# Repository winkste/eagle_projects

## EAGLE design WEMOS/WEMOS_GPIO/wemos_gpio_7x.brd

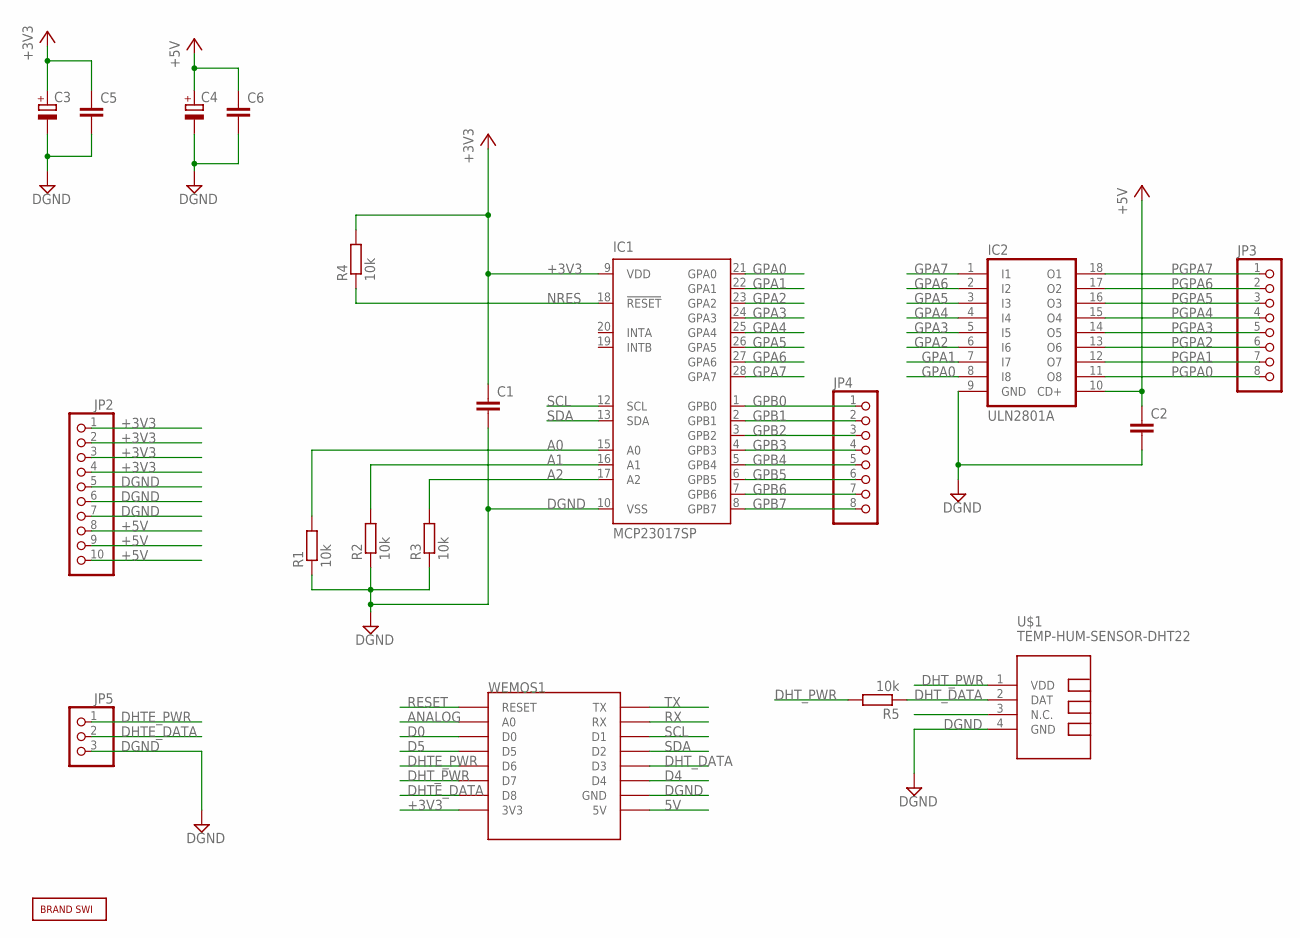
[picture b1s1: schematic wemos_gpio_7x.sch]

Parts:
C1, C2, C5, C6: C-EUC1210; C1210
C3, C4: CPOL-EUTT5D7; TT5D7
IC1: MCP23017SP; DIL28-3
IC2: ULN2801A; DIL18
JP2: PINHD-1X10; 1X10
JP3, JP4: PINHD-1X8; 1X08
JP5: PINHD-1X3; 1X03
R1, R2, R3, R4, R5: 10k; M1206
U$1: TEMP-HUM-SENSOR-DHT22
U$2: BRAND_SWI5X7; BRAND_SWI_5X7
WEMOS1: WEMOS-D1-MINI

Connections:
5V: WEMOS1.5V
+3V3: C1.1, C3.+, C5.1, IC1.9 (VDD), JP2.1, JP2.2, JP2.3, JP2.4, R4.2, WEMOS1.3V3
+5V: C2.1, C4.+, C6.1, IC2.10 (CD+), JP2.8, JP2.9, JP2.10
A0: IC1.15 (A0), R1.2
A1: IC1.16 (A1), R2.2
A2: IC1.17 (A2), R3.2
ANALOG: WEMOS1.A0
D0: WEMOS1.D0
D4: WEMOS1.D4
D5: WEMOS1.D5
DGND: C1.2, C2.2, C3.-, C4.-, C5.2, C6.2, IC1.10 (VSS), IC2.9 (GND), JP2.5, JP2.6, JP2.7, JP5.3, R1.1, R2.1, R3.1, U$1.4 (GND), WEMOS1.GND
DHTE_DATA: JP5.2, WEMOS1.D8
DHTE_PWR: JP5.1, WEMOS1.D6
DHT_DATA: R5.1, U$1.2 (DAT), WEMOS1.D3
DHT_PWR: R5.2, U$1.1 (VDD), WEMOS1.D7
GPA0: IC1.21 (GPA0), IC2.8 (I8)
GPA1: IC1.22 (GPA1), IC2.7 (I7)
GPA2: IC1.23 (GPA2), IC2.6 (I6)
GPA3: IC1.24 (GPA3), IC2.5 (I5)
GPA4: IC1.25 (GPA4), IC2.4 (I4)
GPA5: IC1.26 (GPA5), IC2.3 (I3)
GPA6: IC1.27 (GPA6), IC2.2 (I2)
GPA7: IC1.28 (GPA7), IC2.1 (I1)
GPB0: IC1.1 (GPB0), JP4.1
GPB1: IC1.2 (GPB1), JP4.2
GPB2: IC1.3 (GPB2), JP4.3
GPB3: IC1.4 (GPB3), JP4.4
GPB4: IC1.5 (GPB4), JP4.5
GPB5: IC1.6 (GPB5), JP4.6
GPB6: IC1.7 (GPB6), JP4.7
GPB7: IC1.8 (GPB7), JP4.8
NRES: IC1.18 (!RESET), R4.1
PGPA0: IC2.11 (O8), JP3.8
PGPA1: IC2.12 (O7), JP3.7
PGPA2: IC2.13 (O6), JP3.6
PGPA3: IC2.14 (O5), JP3.5
PGPA4: IC2.15 (O4), JP3.4
PGPA5: IC2.16 (O3), JP3.3
PGPA6: IC2.17 (O2), JP3.2
PGPA7: IC2.18 (O1), JP3.1
RESET: WEMOS1.RESET
RX: WEMOS1.RX
SCL: IC1.12 (SCL), WEMOS1.D1
SDA: IC1.13 (SDA), WEMOS1.D2

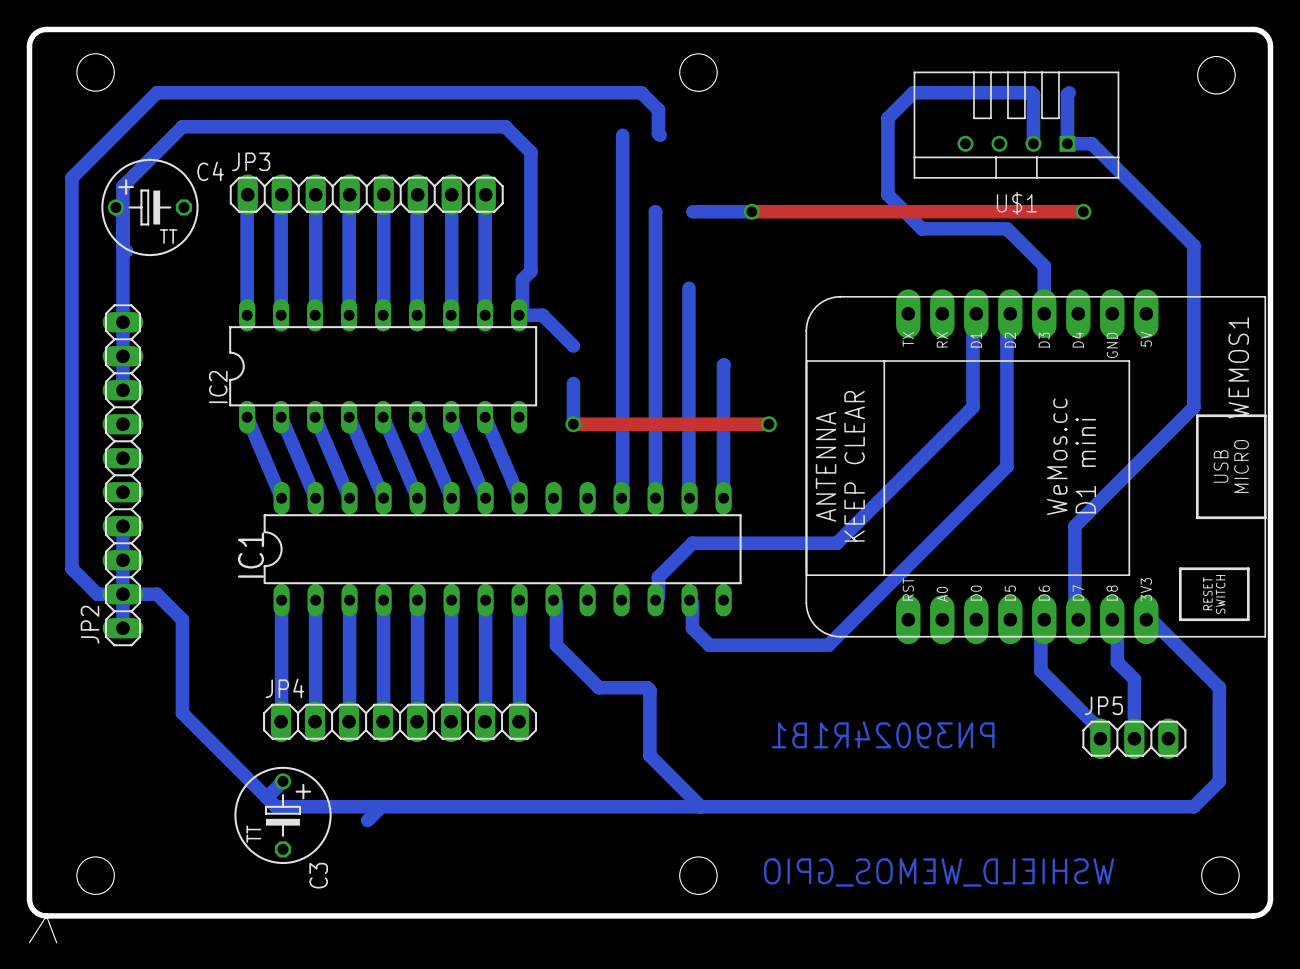
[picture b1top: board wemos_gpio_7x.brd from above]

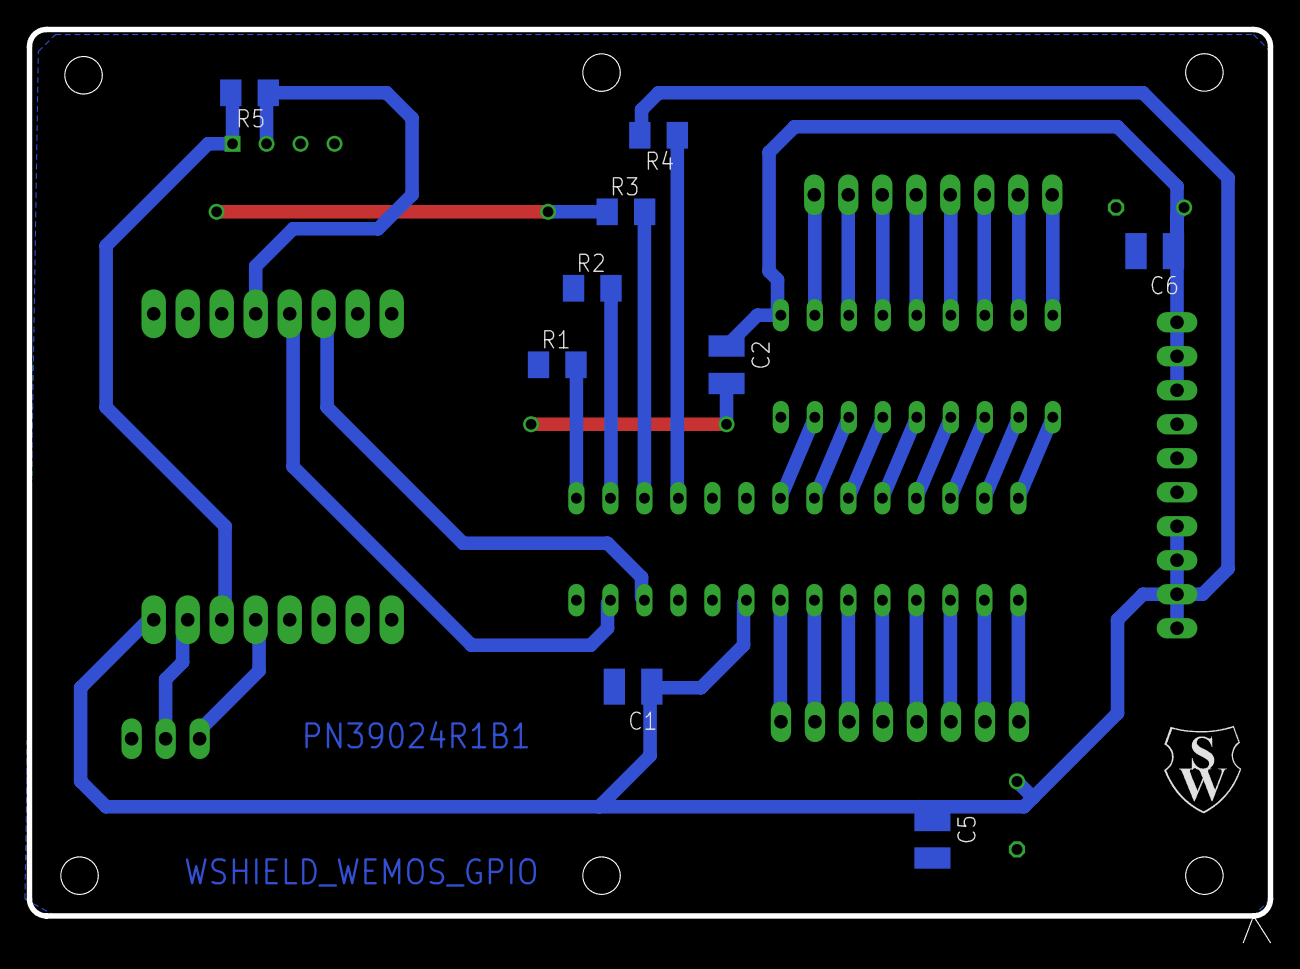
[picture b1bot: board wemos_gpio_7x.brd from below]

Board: 2 copper layers, 92.7 x 68.2 mm, 20 parts (10 on the bottom side), 37 nets.

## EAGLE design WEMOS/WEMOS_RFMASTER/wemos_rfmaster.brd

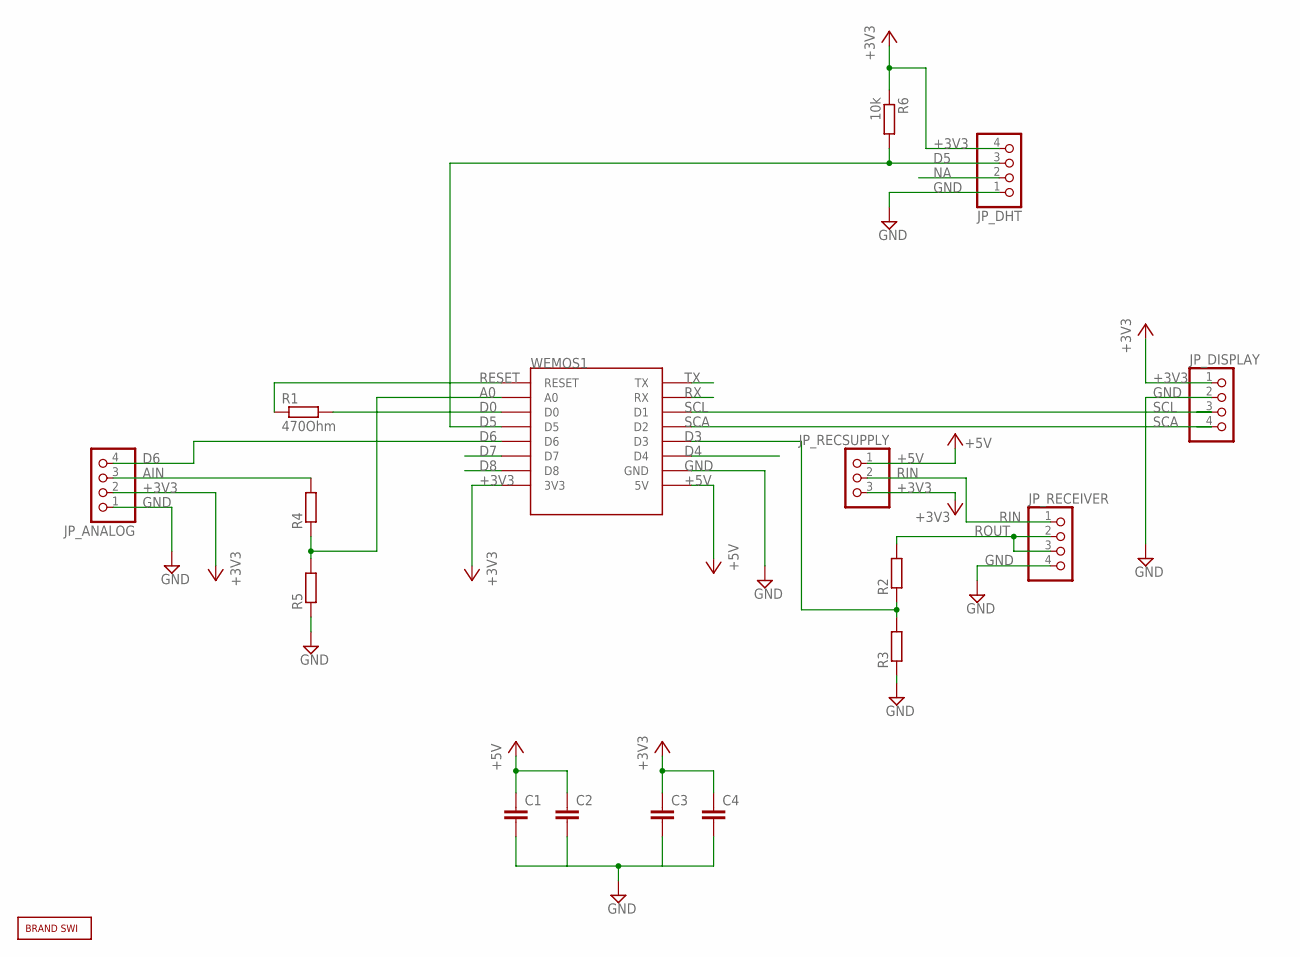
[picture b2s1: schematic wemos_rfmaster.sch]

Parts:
C1, C2, C3, C4: C-EUC1210; C1210
JP_ANALOG: PINHD-1X4; 1X04
JP_DHT: PINHD-1X4; 1X04
JP_DISPLAY: PINHD-1X4; 1X04
JP_RECEIVER: PINHD-1X4; 1X04
JP_RECSUPPLY: PINHD-1X3; 1X03
R1: 470Ohm; R0805
R2, R3, R4, R5: R-EU_R0805; R0805
R6: 10k; R0805
U$2: BRAND_SWI5X7; BRAND_SWI_5X7
WEMOS1: WEMOS-D1-MINI

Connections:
+3V3: C3.1, C4.1, JP_ANALOG.2, JP_DHT.4, JP_DISPLAY.1, JP_RECSUPPLY.3, R6.1, WEMOS1.3V3
+5V: C1.1, C2.1, JP_RECSUPPLY.1, WEMOS1.5V
A0: R4.1, R5.2, WEMOS1.A0
AIN: JP_ANALOG.3, R4.2
D0: R1.2, WEMOS1.D0
D3: R2.1, R3.2, WEMOS1.D3
D4: WEMOS1.D4
D5: JP_DHT.3, R6.2, WEMOS1.D5
D6: JP_ANALOG.4, WEMOS1.D6
D7: WEMOS1.D7
D8: WEMOS1.D8
GND: C1.2, C2.2, C3.2, C4.2, JP_ANALOG.1, JP_DHT.1, JP_DISPLAY.2, JP_RECEIVER.4, R3.1, R5.1, WEMOS1.GND
NA: JP_DHT.2
RESET: R1.1, WEMOS1.RESET
RIN: JP_RECEIVER.1, JP_RECSUPPLY.2
ROUT: JP_RECEIVER.2, JP_RECEIVER.3, R2.2
RX: WEMOS1.RX
SCA: JP_DISPLAY.4, WEMOS1.D2
SCL: JP_DISPLAY.3, WEMOS1.D1
TX: WEMOS1.TX

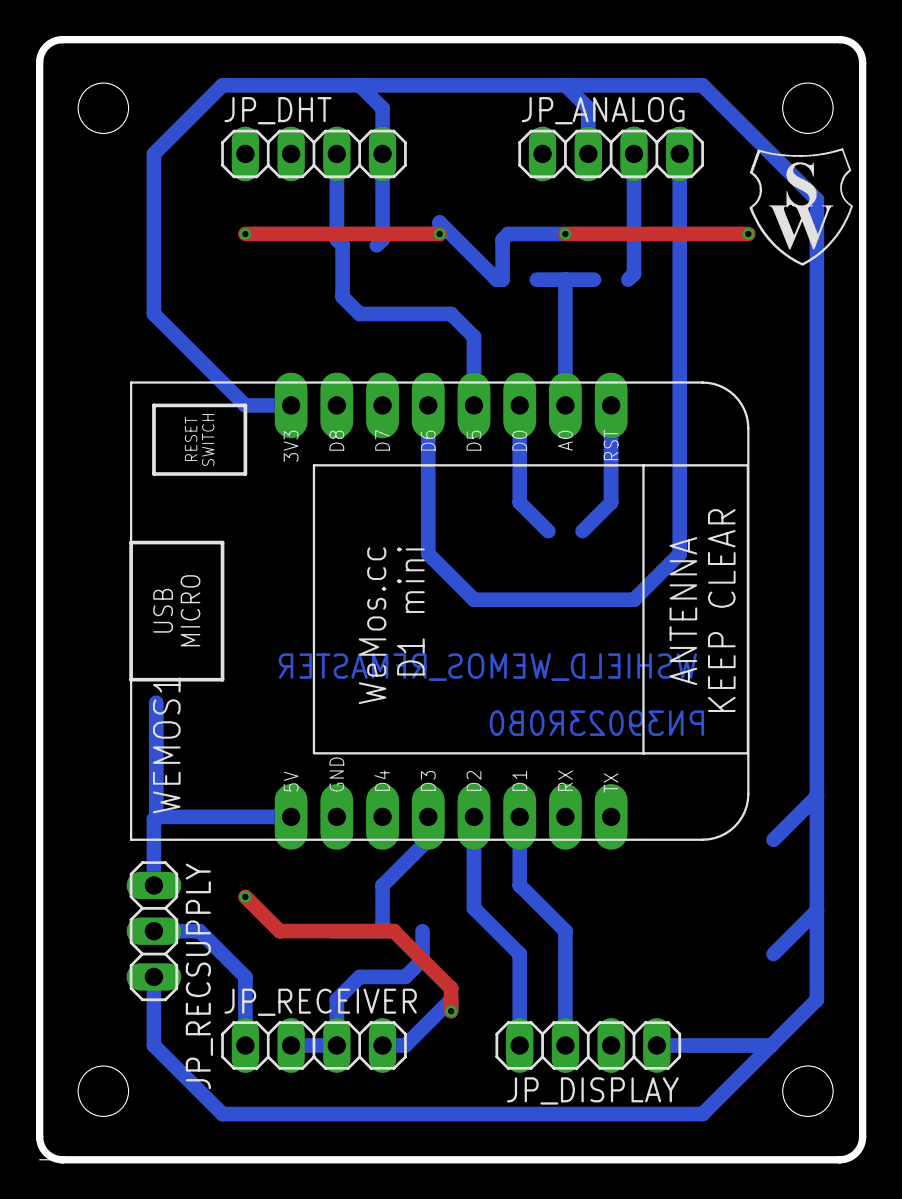
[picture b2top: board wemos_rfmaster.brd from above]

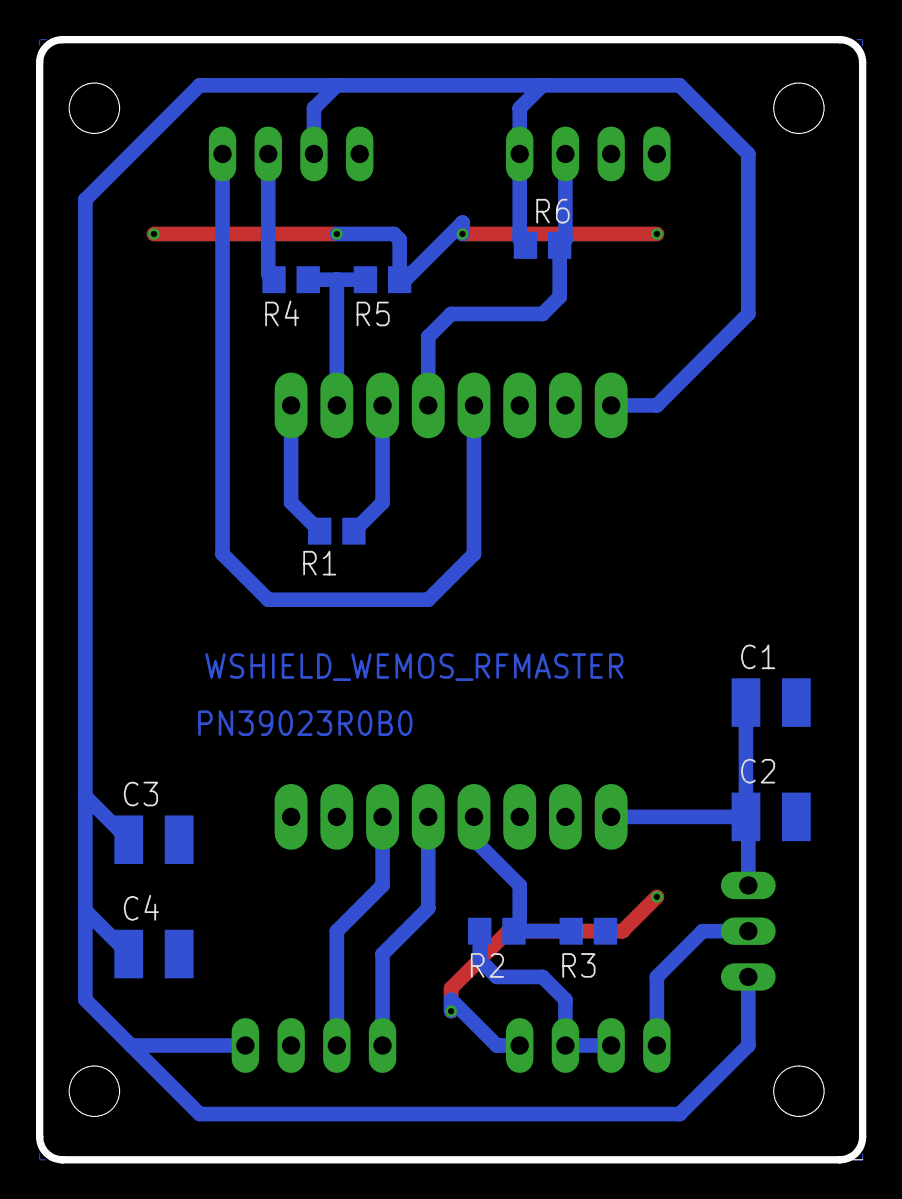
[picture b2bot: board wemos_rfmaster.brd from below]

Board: 2 copper layers, 45.7 x 62.2 mm, 17 parts (10 on the bottom side), 14 nets.

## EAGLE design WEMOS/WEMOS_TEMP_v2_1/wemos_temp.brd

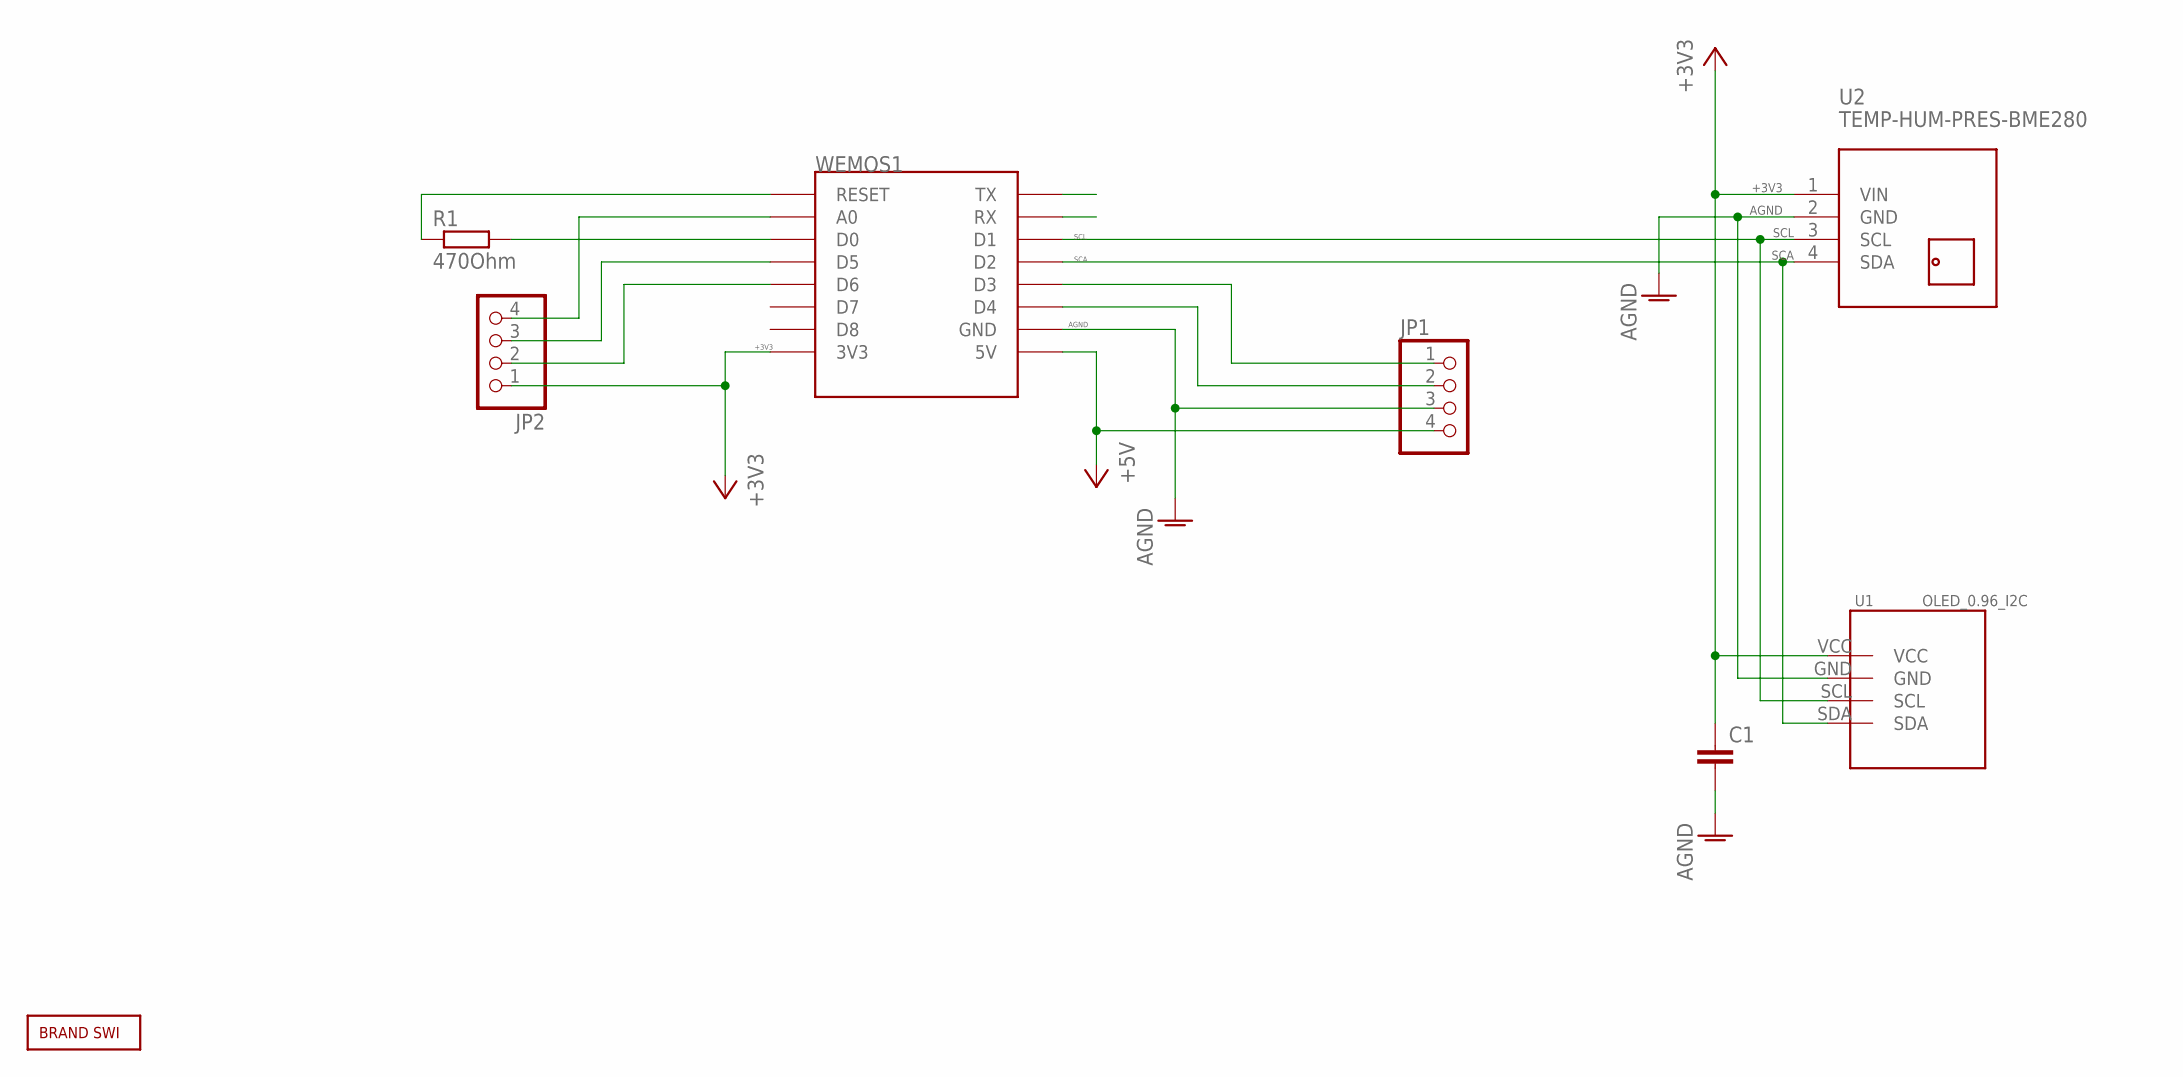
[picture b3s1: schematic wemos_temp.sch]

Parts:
C1: C-EUC1210; C1210
JP1, JP2: PINHD-1X4; 1X04
R1: 470Ohm; R0805
U1: OLED_0.96_I2C
U2: TEMP-HUM-PRES-BME280
U$2: BRAND_SWI5X7; BRAND_SWI_5X7
WEMOS1: WEMOS-D1-MINI

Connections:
+3V3: C1.1, JP2.1, U1.VCC, U2.1 (VIN), WEMOS1.3V3
+5V: JP1.4, WEMOS1.5V
AGND: C1.2, JP1.3, U1.GND, U2.2 (GND), WEMOS1.GND
D4: JP1.2, WEMOS1.D4
unnamed: R1.1, WEMOS1.RESET
unnamed: R1.2, WEMOS1.D0
unnamed: JP1.1, WEMOS1.D3
unnamed: JP2.4, WEMOS1.A0
unnamed: JP2.3, WEMOS1.D5
unnamed: JP2.2, WEMOS1.D6
RX: WEMOS1.RX
SCA: U1.SDA, U2.4 (SDA), WEMOS1.D2
SCL: U1.SCL, U2.3 (SCL), WEMOS1.D1
TX: WEMOS1.TX

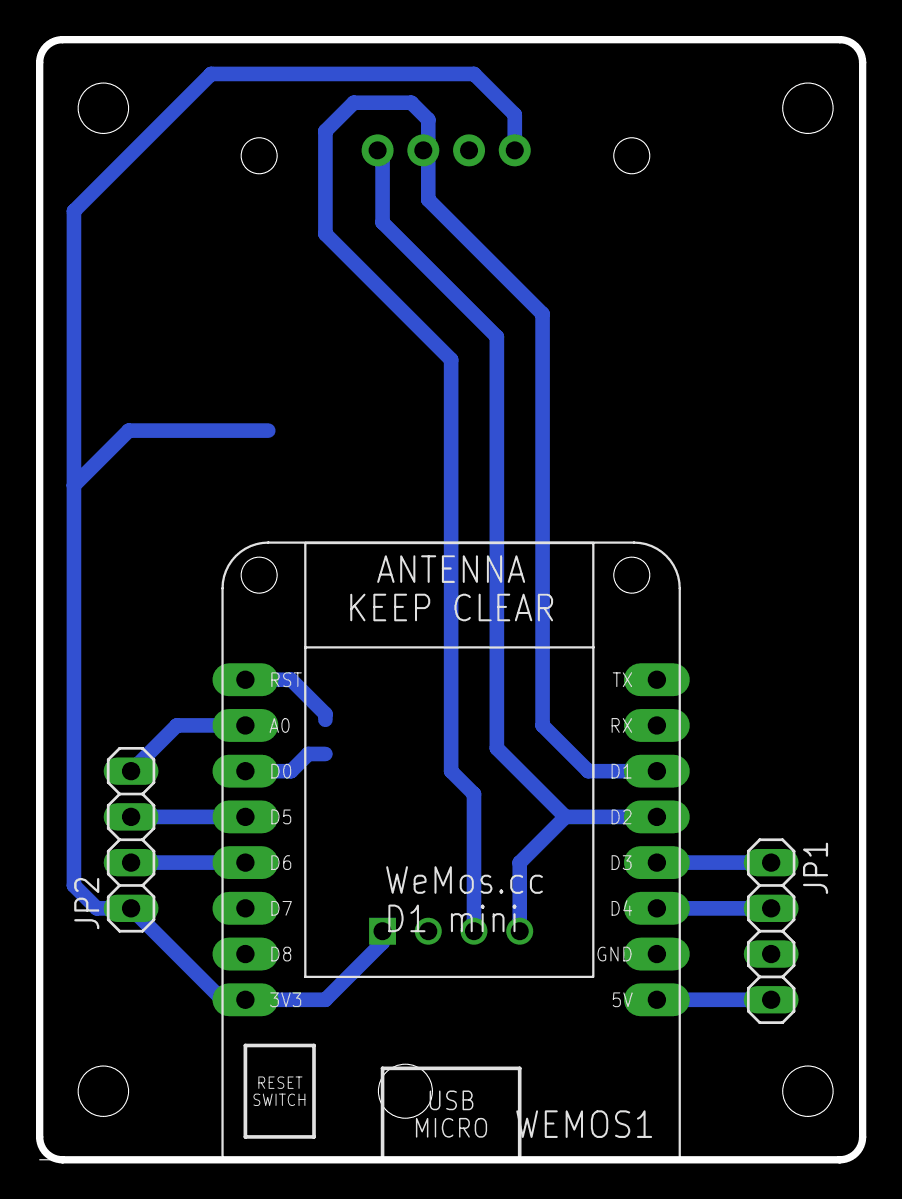
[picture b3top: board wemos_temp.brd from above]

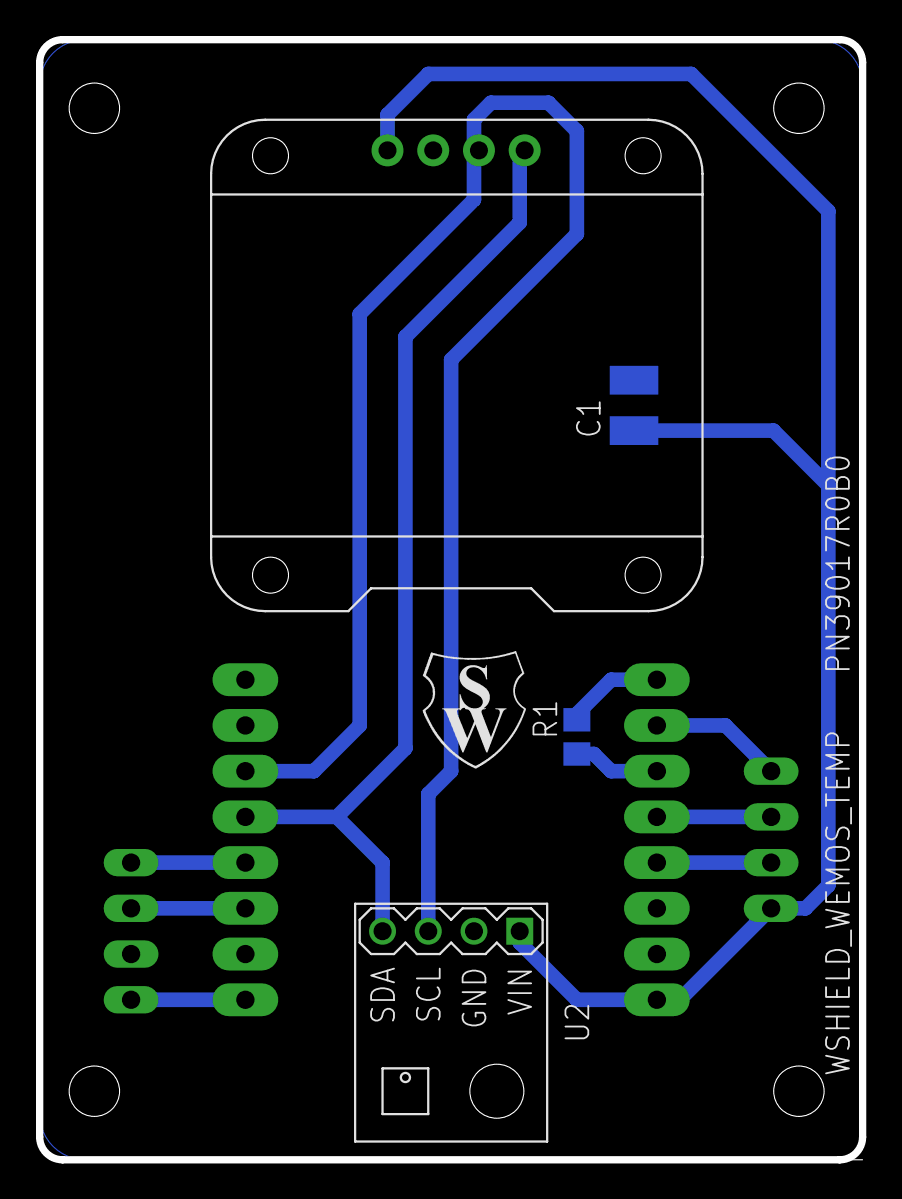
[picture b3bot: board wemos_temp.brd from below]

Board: 2 copper layers, 45.7 x 62.2 mm, 8 parts (5 on the bottom side), 12 nets.

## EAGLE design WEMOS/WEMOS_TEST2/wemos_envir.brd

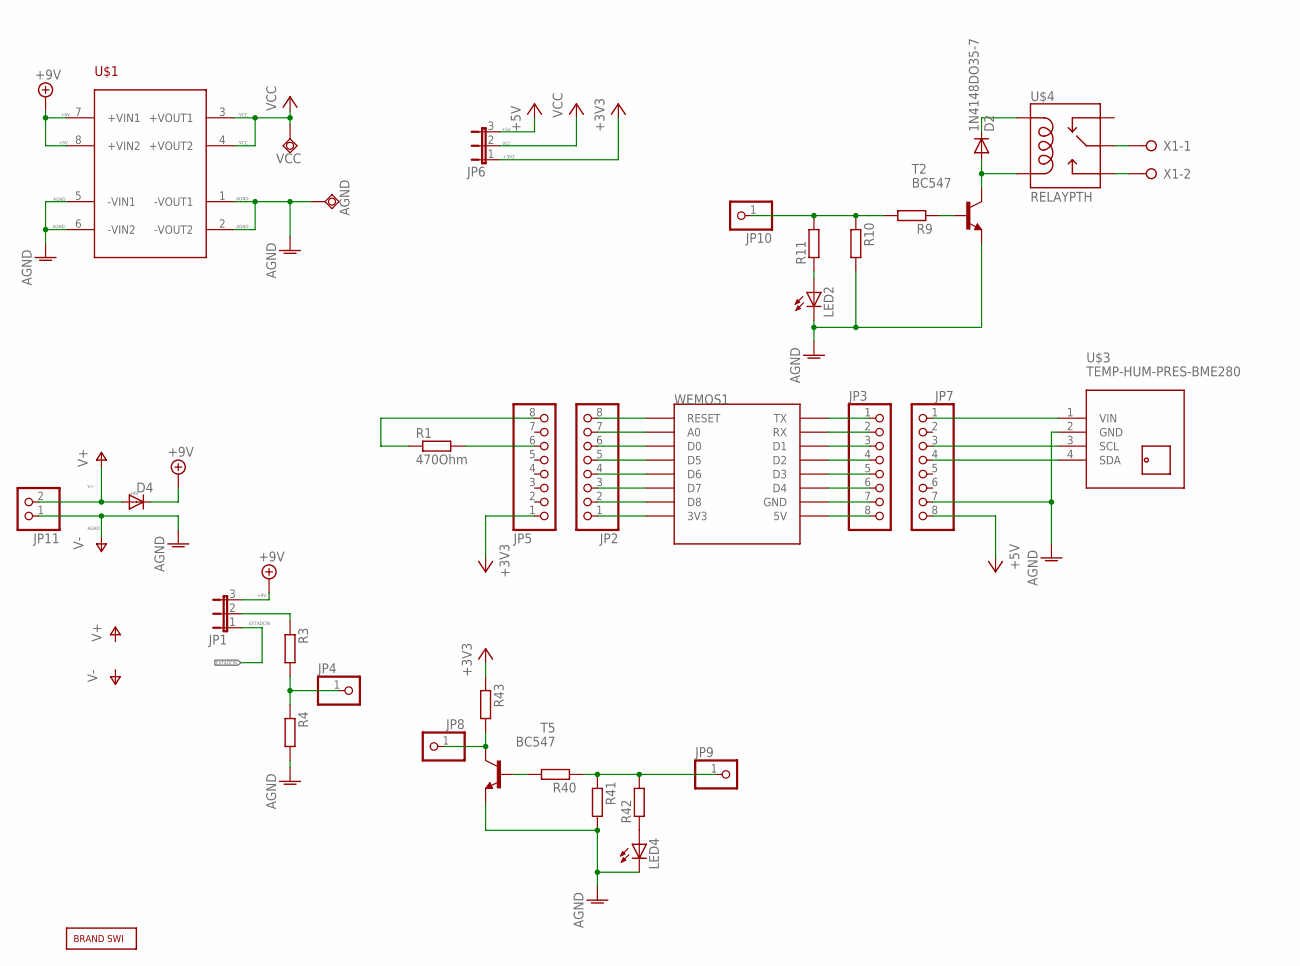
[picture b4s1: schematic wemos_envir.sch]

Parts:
AGND: TPSQTP20SQ; TP20SQ
D2, D4: 1N4148DO35-7; DO35-7
JP1, JP6: JP2E; JP2
JP2, JP3, JP5, JP7: PINHD-1X8; 1X08
JP4, JP8, JP9, JP10: PINHD-1X1; 1X01
JP11: PINHD-1X2; 1X02
LED2, LED4: LEDCHIP-LED0805; CHIP-LED0805
R1: 470Ohm; R0805
R3, R4, R9, R10, R11, R40, R41, R42, R43: R-EU_R0805; R0805
T2, T5: BC547; TO92
U$1: LVPS
U$2: BRAND_SWI5X7; BRAND_SWI_5X7
U$3: TEMP-HUM-PRES-BME280
U$4: RELAYPTH; SRD-05VDC-SL-C
VCC: TPSQTP20SQ; TP20SQ
WEMOS1: WEMOS-D1-MINI
X1: W237-02P; W237-132

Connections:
+3V3: JP5.1, JP6.1, R43.1
+5V: JP6.3, JP7.8
+9V: D4.C, JP1.3, U$1.7 (+VIN1), U$1.8 (+VIN2)
ADCIN: JP4.1, R3.2, R4.1
AGND: AGND.TP, JP7.7, JP11.1, LED2.C, LED4.C, R4.2, R10.2, R41.2, T2.1 (E), T5.1 (E), U$1.2 (-VOUT2), U$1.5 (-VIN1), U$1.6 (-VIN2), U$3.2 (GND)
EXTADCIN: JP1.1
unnamed: JP1.2, R3.1
unnamed: JP5.6, R1.2
unnamed: D2.C, U$4.COIL1
unnamed: D2.A, T2.3 (C), U$4.COIL0
unnamed: R9.1, T2.2 (B)
unnamed: JP10.1, R9.2, R10.1, R11.2
unnamed: LED2.A, R11.1
unnamed: U$4.SWOPEN, X1.2
unnamed: U$4.SWCOMMON, X1.1
unnamed: JP5.8, R1.1
unnamed: JP2.7, WEMOS1.A0
unnamed: JP2.8, WEMOS1.RESET
unnamed: JP2.6, WEMOS1.D0
unnamed: JP2.5, WEMOS1.D5
unnamed: JP2.4, WEMOS1.D6
unnamed: JP2.3, WEMOS1.D7
unnamed: JP2.2, WEMOS1.D8
unnamed: JP2.1, WEMOS1.3V3
unnamed: JP3.3, WEMOS1.D1
unnamed: JP3.4, WEMOS1.D2
unnamed: JP3.1, WEMOS1.TX
unnamed: JP3.2, WEMOS1.RX
unnamed: JP3.6, WEMOS1.D4
unnamed: JP3.7, WEMOS1.GND
unnamed: JP3.8, WEMOS1.5V
unnamed: JP3.5, WEMOS1.D3
unnamed: R40.2, T5.2 (B)
unnamed: JP7.1, U$3.1 (VIN)
unnamed: LED4.A, R42.1
PCTRL: JP9.1, R40.1, R41.1, R42.2
PVIN: JP8.1, R43.2, T5.3 (C)
SCA: JP7.4, U$3.4 (SDA)
SCL: JP7.3, U$3.3 (SCL)
V+: D4.A, JP11.2
VCC: JP6.2, U$1.3 (+VOUT1), U$1.4 (+VOUT2), VCC.TP

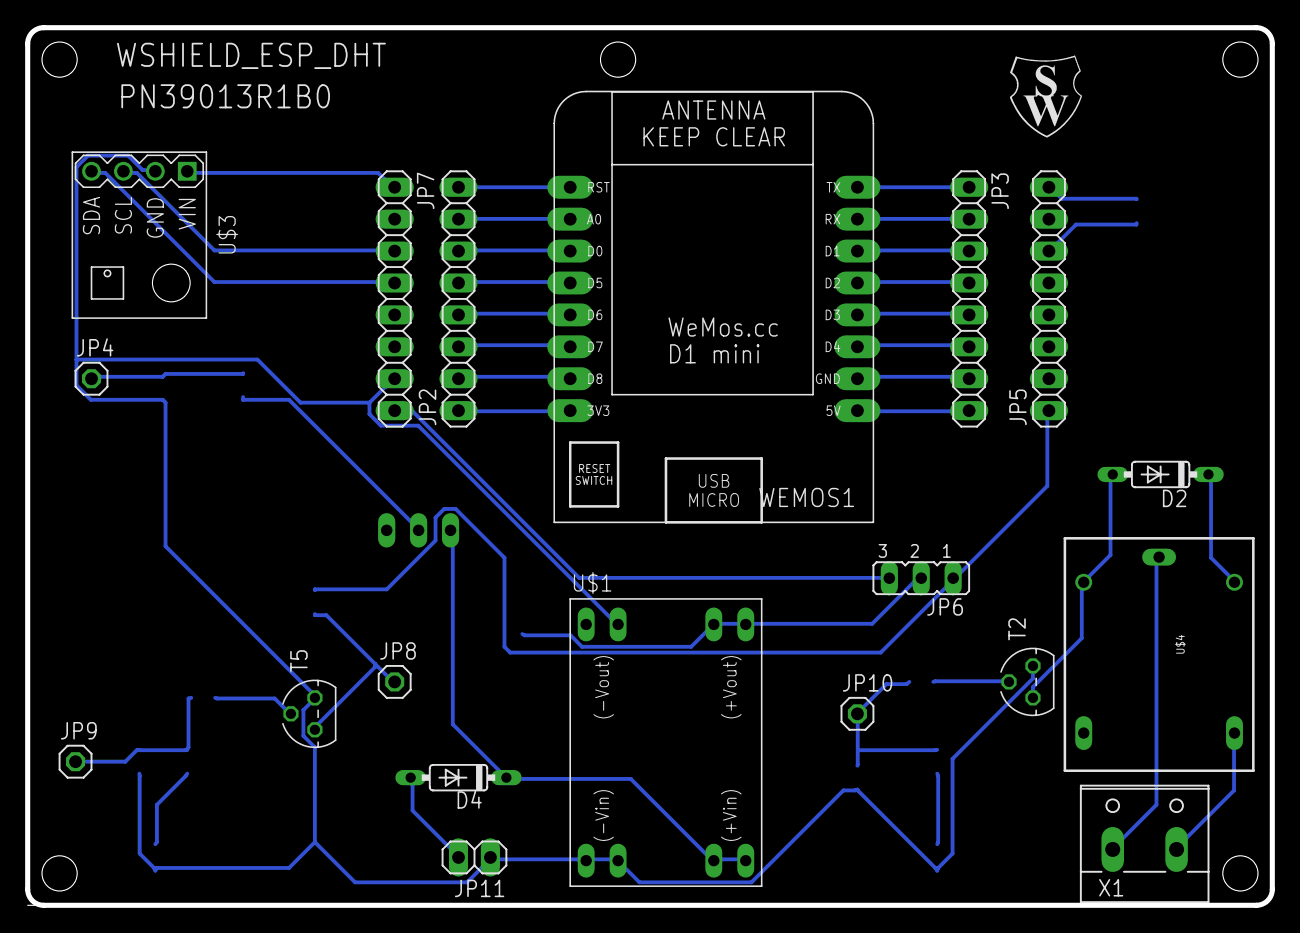
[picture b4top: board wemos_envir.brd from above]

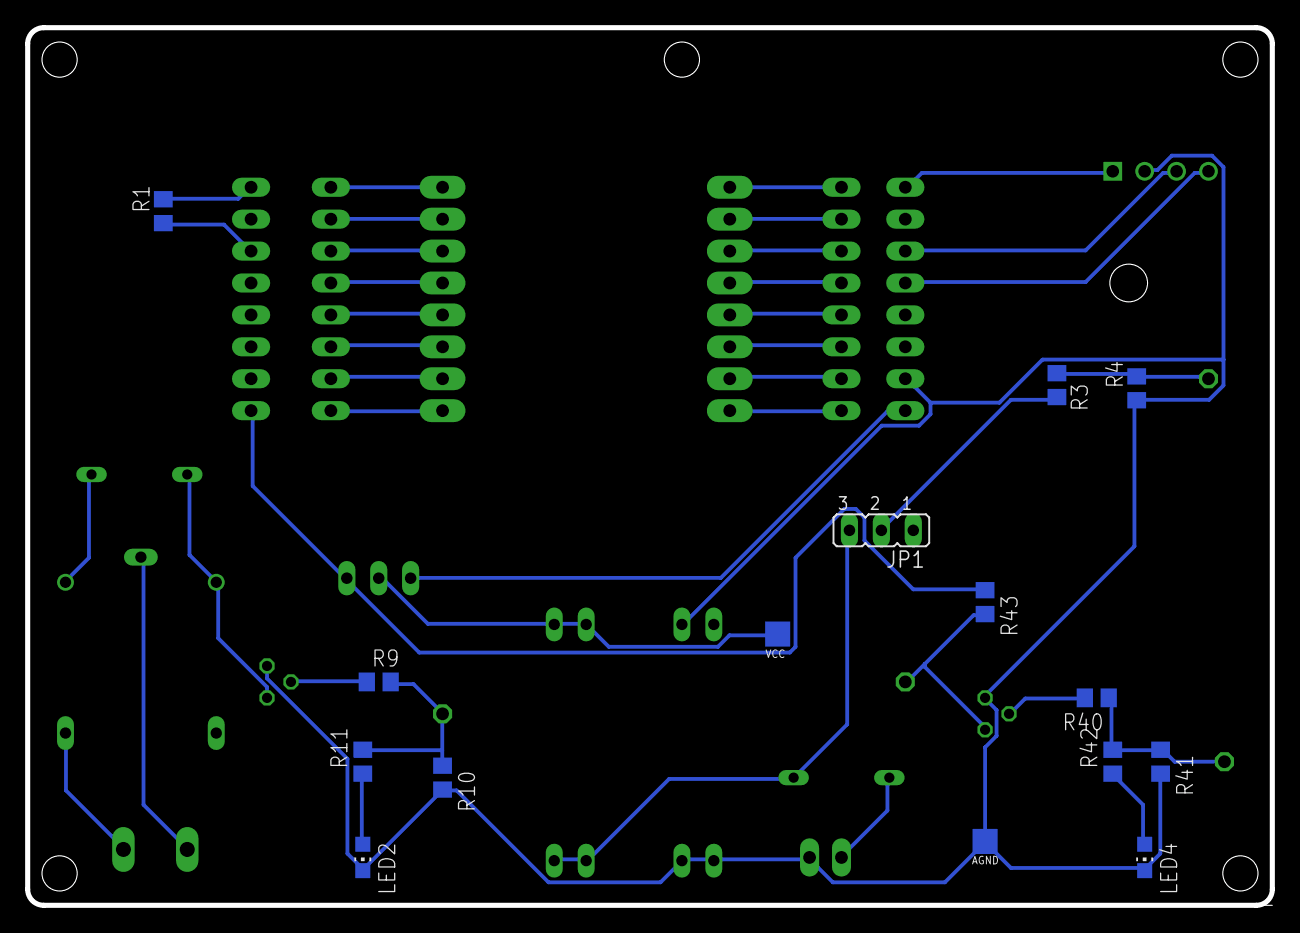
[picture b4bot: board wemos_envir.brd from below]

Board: 2 copper layers, 99.1 x 69.8 mm, 35 parts (15 on the bottom side), 40 nets.

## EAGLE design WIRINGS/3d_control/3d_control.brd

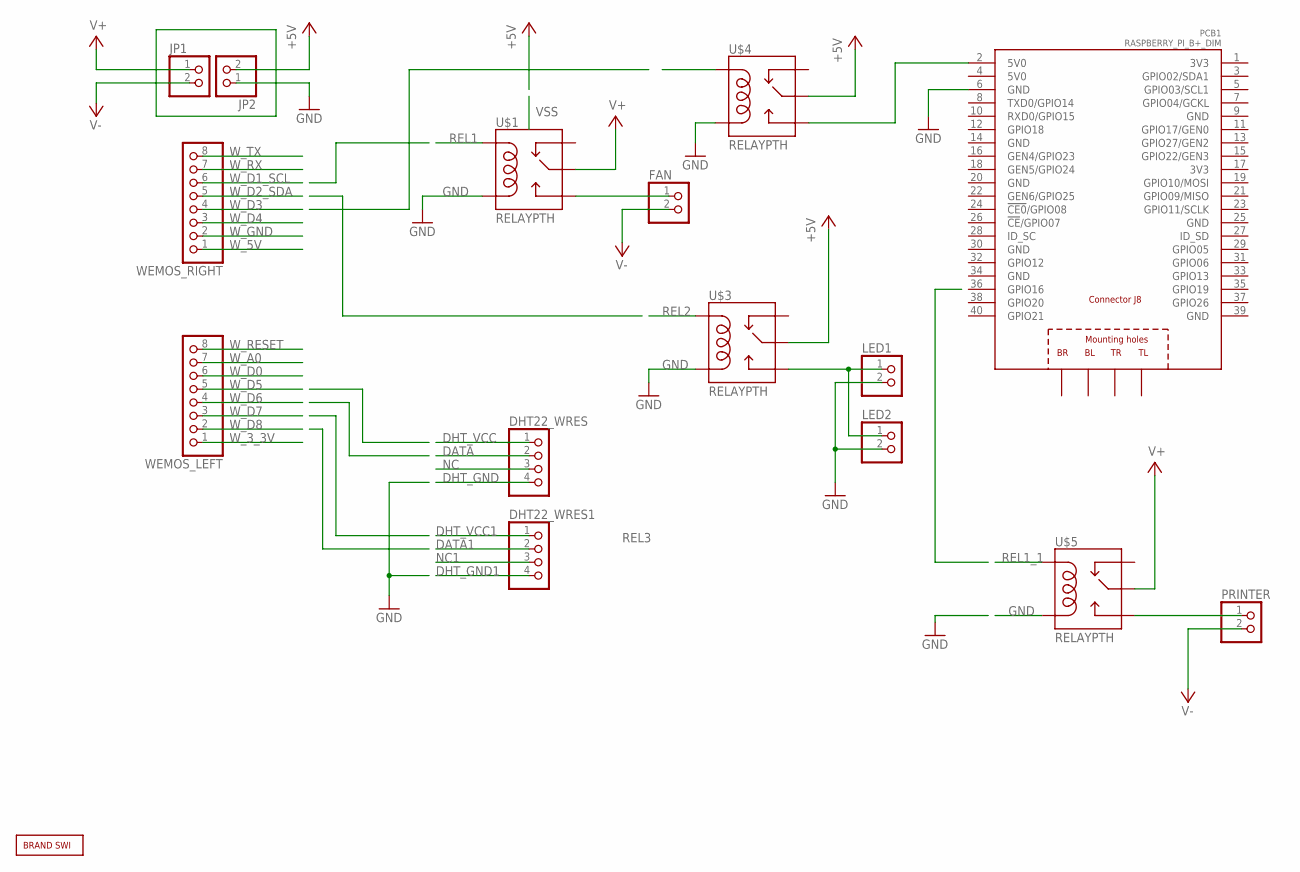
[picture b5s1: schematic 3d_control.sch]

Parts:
DHT22_WRES, DHT22_WRES1: PINHD-1X4; 1X04
FAN: PINHD-1X2; 1X02
JP1, JP2: PINHD-1X2; 1X02
LED1, LED2: PINHD-1X2; 1X02
PCB1: RASPBERRY_PI_B+_DIM; RASPBERRY_PI_BPLUS_DIM
PRINTER: PINHD-1X2; 1X02
U$1, U$3, U$4, U$5: RELAYPTH; SRD-05VDC-SL-C
U$2: BRAND_SWI5X7; BRAND_SWI_5X7
WEMOS_LEFT: PINHD-1X8; 1X08
WEMOS_RIGHT: PINHD-1X8; 1X08

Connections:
3V3: PCB1.1 (3V3), PCB1.17 (3V3)
5V0: PCB1.4 (5V0)
+5V: JP2.2, U$3.SWCOMMON, U$4.SWCOMMON
DATA: DHT22_WRES.2
DATA1: DHT22_WRES1.2
DHT_GND: DHT22_WRES.4
DHT_GND1: DHT22_WRES1.4
DHT_VCC: DHT22_WRES.1
DHT_VCC1: DHT22_WRES1.1
GND: JP2.1, LED1.2, LED2.2, PCB1.6 (GND), PCB1.9 (GND), PCB1.14 (GND), PCB1.20 (GND), PCB1.25 (GND), PCB1.30 (GND), PCB1.34 (GND), PCB1.39 (GND), U$1.COIL0, U$3.COIL0, U$4.COIL0, U$5.COIL0
unnamed: LED1.1, LED2.1
unnamed: FAN.1, U$1.SWOPEN
unnamed: PCB1.2 (5V0), U$4.SWOPEN
unnamed: PRINTER.1, U$5.SWOPEN
NC: DHT22_WRES.3
NC1: DHT22_WRES1.3
REL1: U$1.COIL1
REL1_1: U$5.COIL1
REL2: U$3.COIL1
REL3: U$4.COIL1
V+: JP1.1, U$1.SWCOMMON, U$5.SWCOMMON
V-: FAN.2, JP1.2, PRINTER.2
W_3_3V: WEMOS_LEFT.1
W_5V: WEMOS_RIGHT.1
W_A0: WEMOS_LEFT.7
W_D0: WEMOS_LEFT.6
W_D1_SCL: WEMOS_RIGHT.6
W_D2_SDA: WEMOS_RIGHT.5
W_D3: WEMOS_RIGHT.4
W_D4: WEMOS_RIGHT.3
W_D5: WEMOS_LEFT.5
W_D6: WEMOS_LEFT.4
W_D7: WEMOS_LEFT.3
W_D8: WEMOS_LEFT.2
W_GND: WEMOS_RIGHT.2
W_RESET: WEMOS_LEFT.8
W_RX: WEMOS_RIGHT.7
W_TX: WEMOS_RIGHT.8

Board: 2 copper layers, 16 parts (1 on the bottom side), 9 nets, no tracks yet.

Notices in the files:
parts and their libraries:
diy-modules: Released under the Creative Commons Attribution 4.0 International License: http://creativecommons.org/licenses/by/4.0
